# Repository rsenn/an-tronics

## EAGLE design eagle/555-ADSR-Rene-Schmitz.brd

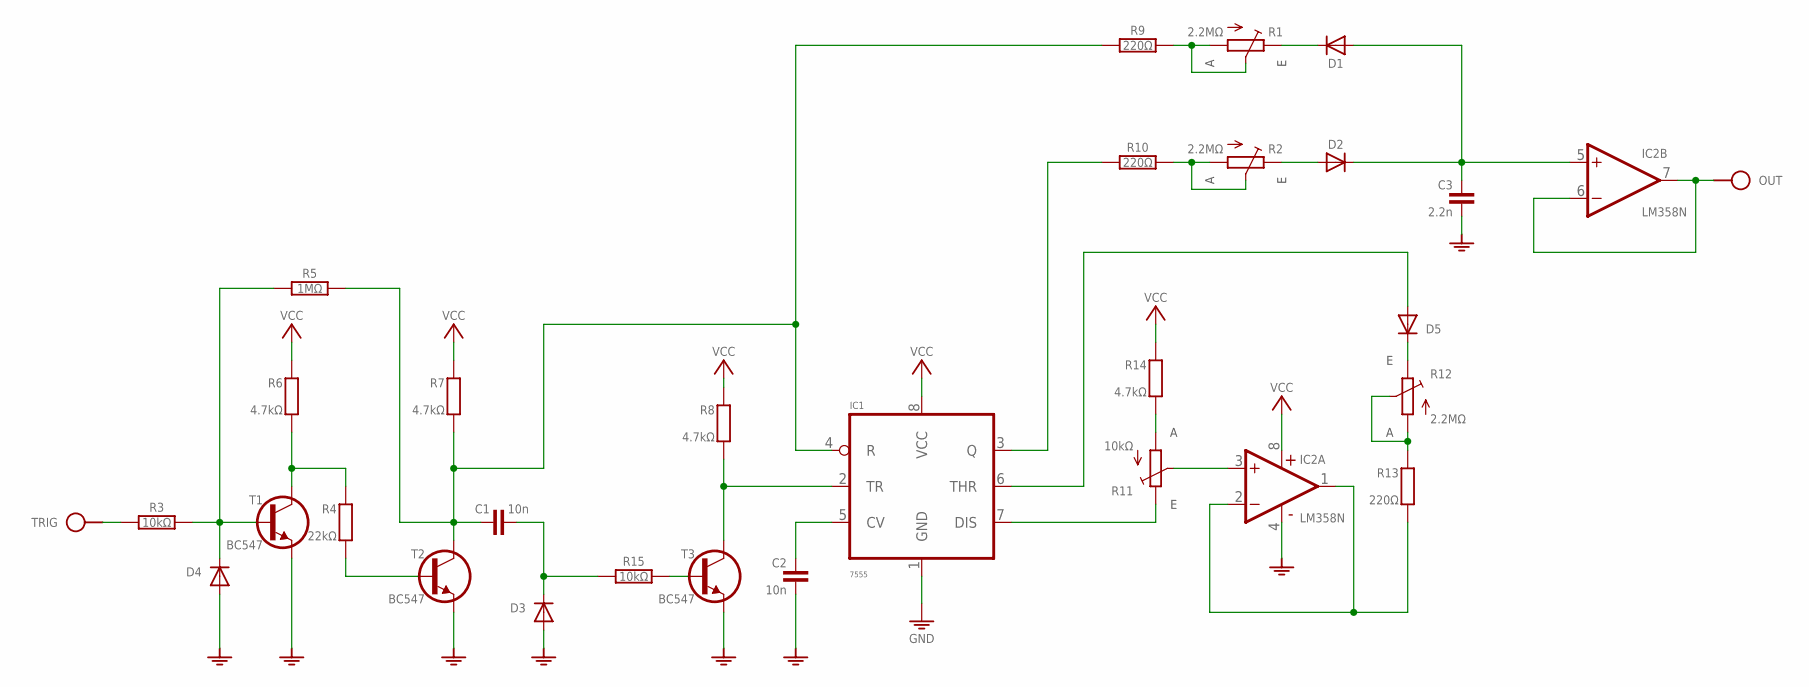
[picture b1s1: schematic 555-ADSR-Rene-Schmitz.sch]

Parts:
C1: 10n; C050-020X044
C2: 10n; C050-025X075/V
C3: 2.2n; C050-025X075/V
D1, D2: DIODE-HDO34-7; DO34-7
D3, D4, D5: DIODE34-7V; DO34-7V
IC1: 7555; DIL08
IC2: LM358N; DIL08
OUT: SPAD
R1, R2, R12: 2.2MΩ; R-TRIM
R3, R15: 10kΩ; 0204/10
R4: 22kΩ; 0204/10-V
R5: 1MΩ; 0204/10
R6, R7, R8, R14: 4.7kΩ; 0204/10
R9, R10: 220Ω; 0204/10
R11: 10kΩ; R-TRIM
R13: 220Ω; 0204/10-V
S2: VCC_GNDL; SPAD-+
T1, T2, T3: BC547; TO92-CBE
TRIG: SPAD

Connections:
GND: C2.2, C3.2, D3.A, D4.A, IC1.1 (GND), IC2.4 (V-), S2.1 (GND), T1.E, T2.E, T3.E
unnamed: R4.1, R6.2, T1.C
unnamed: R4.2, T2.B
unnamed: IC2.3 (+IN), R11.2 (S)
unnamed: D4.C, R3.2, R5.1, T1.B
unnamed: R15.2, T3.B
unnamed: R1.1 (A), R1.2 (S), R9.2
unnamed: R2.1 (A), R2.2 (S), R10.2
unnamed: R3.1, TRIG.1
unnamed: C1.1, IC1.4 (R), R5.2, R7.2, R9.1, T2.C
unnamed: IC1.2 (TR), R8.2, T3.C
unnamed: IC2.6 (-IN), IC2.7 (OUT), OUT.1
unnamed: C2.1, IC1.5 (CV)
unnamed: R12.1 (A), R12.2 (S), R13.1
unnamed: R11.1 (A), R14.2
unnamed: IC1.7 (DIS), R11.3 (E)
unnamed: D5.A, IC1.6 (THR)
unnamed: D5.C, R12.3 (E)
unnamed: C1.2, D3.C, R15.1
unnamed: IC1.3 (Q), R10.1
unnamed: D2.A, R2.3 (E)
unnamed: D1.C, R1.3 (E)
unnamed: IC2.1 (OUT), IC2.2 (-IN), R13.2
unnamed: C3.1, D1.A, D2.C, IC2.5 (+IN)
VCC: IC1.8 (VCC), IC2.8 (V+), R6.1, R7.1, R8.1, R14.1, S2.2 (VCC)

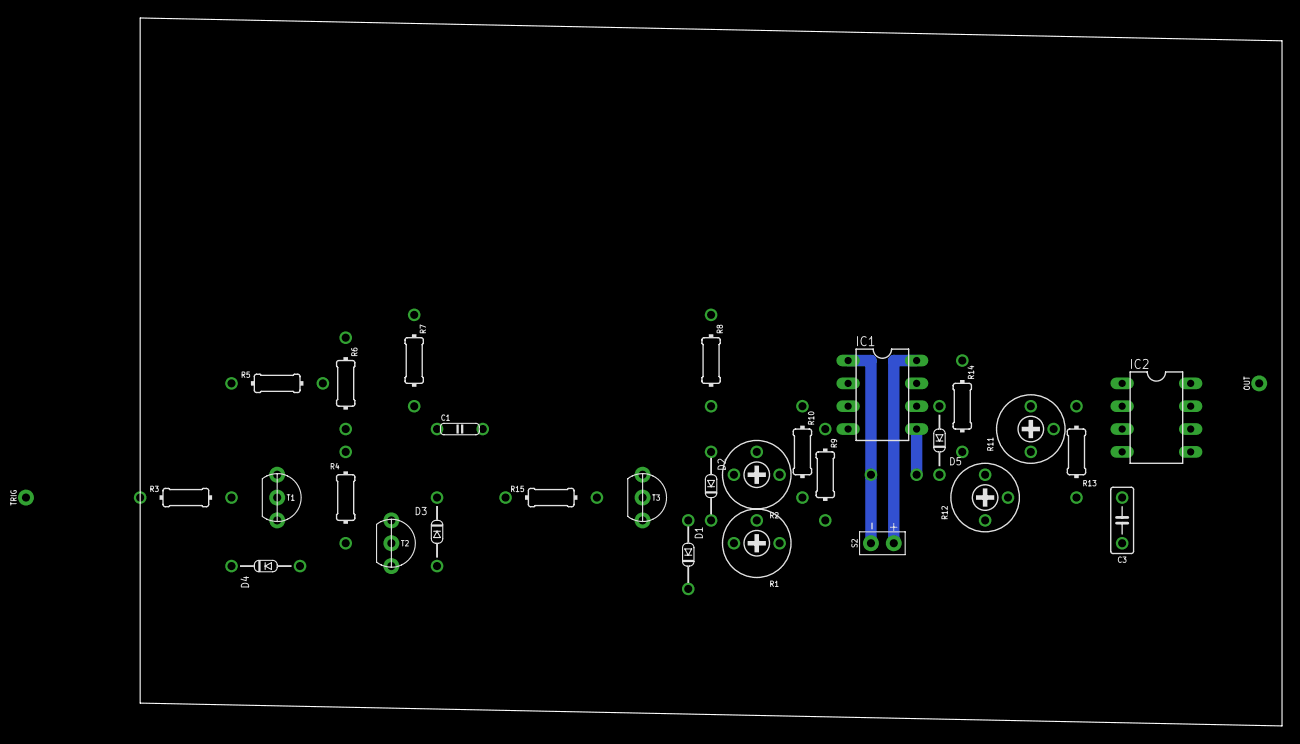
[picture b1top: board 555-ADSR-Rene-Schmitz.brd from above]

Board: 2 copper layers, 127.0 x 78.7 mm, 31 parts (1 on the bottom side), 25 nets.

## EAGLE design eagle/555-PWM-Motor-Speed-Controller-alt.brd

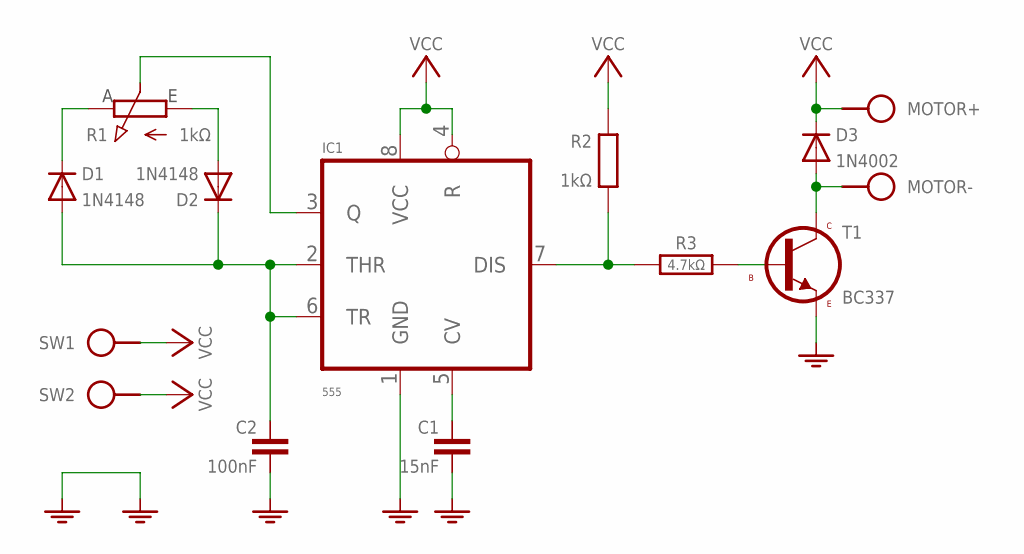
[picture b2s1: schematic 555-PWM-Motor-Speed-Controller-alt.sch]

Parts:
C1: 15nF; C050-020X036/V
C2: 100nF; C025-015X024/V
D1: 1N4148; DO34-5V
D2: 1N4148; DO34-5-V
D3: 1N4002; DO34-5V
IC1: 555; DIL08
MOTOR: SPAD+-+-; SPAD+-
PWR: VCC_GNDR; SPAD+-
R1: 1kΩ; CONN-3P/H
R2: 1kΩ; 0204/10-V
R3: 4.7kΩ; 0204/10-V
SW1, SW2: SPAD-1; SPAD
T1: BC337; TO92-CBE

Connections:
GND: C1.2, C2.2, IC1.1 (GND), PWR.1 (GND), T1.3 (E)
unnamed: C1.1, IC1.5 (CV)
unnamed: IC1.7 (DIS), R2.2 (1), R3.1
unnamed: IC1.3 (Q), R1.2 (S)
unnamed: D1.C, R1.3 (E)
unnamed: D2.A, R1.1 (A)
unnamed: C2.1, D1.A, D2.C, IC1.2 (THR), IC1.6 (TR)
unnamed: R3.2, T1.2 (B)
unnamed: D3.A, MOTOR.1, T1.1 (C)
PWR+: PWR.2 (VCC), SW1.1
VCC: D3.C, IC1.4 (R), IC1.8 (VCC), MOTOR.2, R2.1 (2), SW2.1

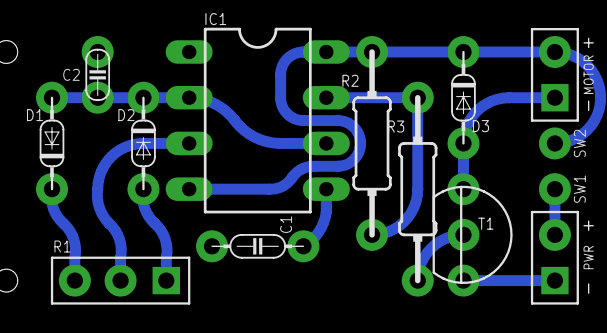
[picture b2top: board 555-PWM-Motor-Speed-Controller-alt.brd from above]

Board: 2 copper layers, 14 parts (0 on the bottom side), 11 nets.

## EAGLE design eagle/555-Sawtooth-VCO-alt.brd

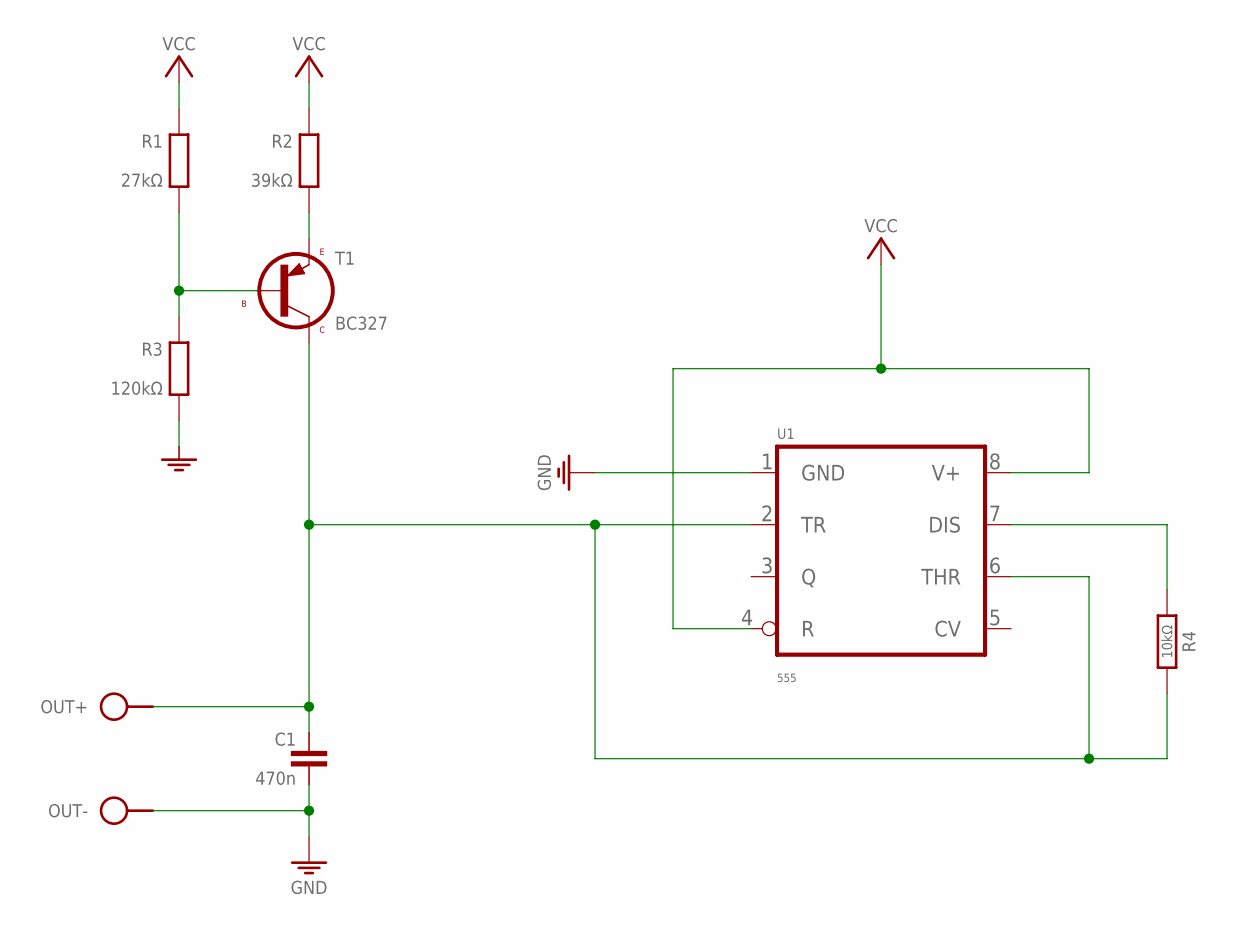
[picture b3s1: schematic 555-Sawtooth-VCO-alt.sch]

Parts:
C1: 470n; C075-020X044/V
OUT: SPAD+--+; SPAD-+
R1: 27kΩ; 0207/10
R2: 39kΩ; 0207/10
R3: 120kΩ; 0207/10
R4: 10kΩ; 0204/10
S3, S4, S5: VCC_GNDPWR-R; PWR-R
T1: BC327; TO92
U1: 555; DIL08

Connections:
DIS: C1.1, OUT.2, R4.2, T1.1 (C), U1.2 (TR), U1.6 (THR)
GND: C1.2, OUT.1, R3.2 (1), S4.1 (GND), S5.1 (GND), U1.1 (GND)
unnamed: R4.1, U1.7 (DIS)
unnamed: R2.2 (1), T1.3 (E)
unnamed: R1.2 (1), R3.1 (2), T1.2 (B)
VCC: R1.1 (2), R2.1 (2), S3.2 (VCC), U1.4 (R), U1.8 (V+)

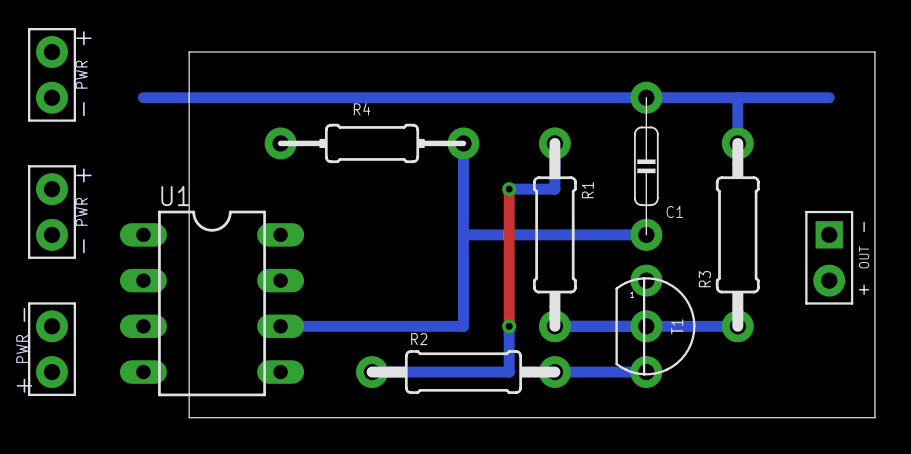
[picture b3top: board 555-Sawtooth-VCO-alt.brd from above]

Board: 2 copper layers, 38.1 x 20.3 mm, 11 parts (0 on the bottom side), 6 nets.

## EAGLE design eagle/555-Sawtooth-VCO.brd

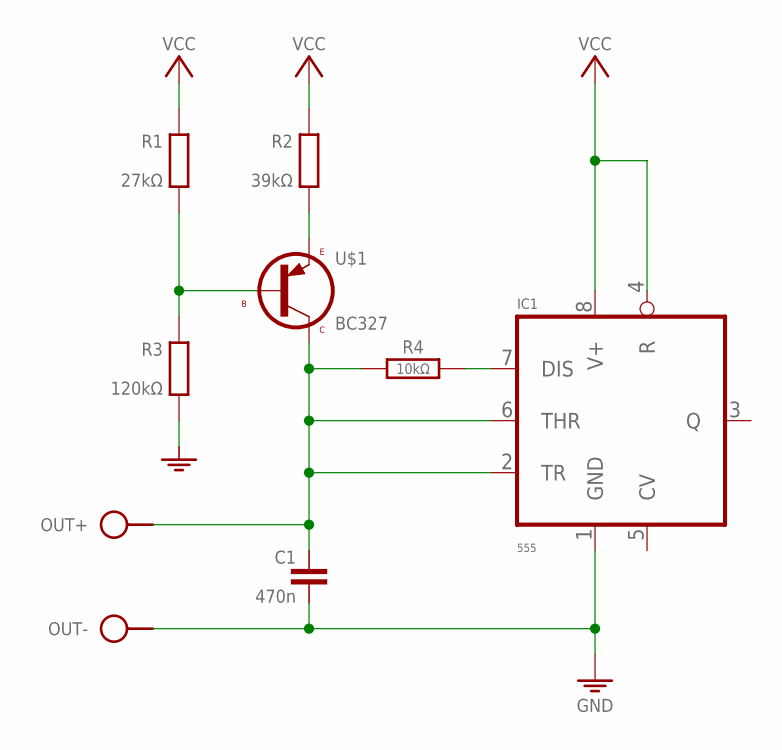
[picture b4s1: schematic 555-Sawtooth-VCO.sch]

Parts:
C1: 470n; C075-020X044/V
IC1: 555; DIL08
OUT: SPAD+--+; SPAD-+
R1: 27kΩ; 0207/10
R2: 39kΩ; 0207/10
R3: 120kΩ; 0207/10
R4: 10kΩ; 0204/10
S1: VCC_GNDPWR-R; PWR-R
U$1: BC327; TO92

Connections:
GND: C1.2, IC1.1 (GND), OUT.1, R3.2 (1), S1.1 (GND)
unnamed: IC1.7 (DIS), R4.2
unnamed: R2.2 (1), U$1.3 (E)
unnamed: R1.2 (1), R3.1 (2), U$1.2 (B)
TR: C1.1, IC1.2 (TR), IC1.6 (THR), OUT.2, R4.1, U$1.1 (C)
VCC: IC1.4 (R), IC1.8 (V+), R1.1 (2), R2.1 (2), S1.2 (VCC)

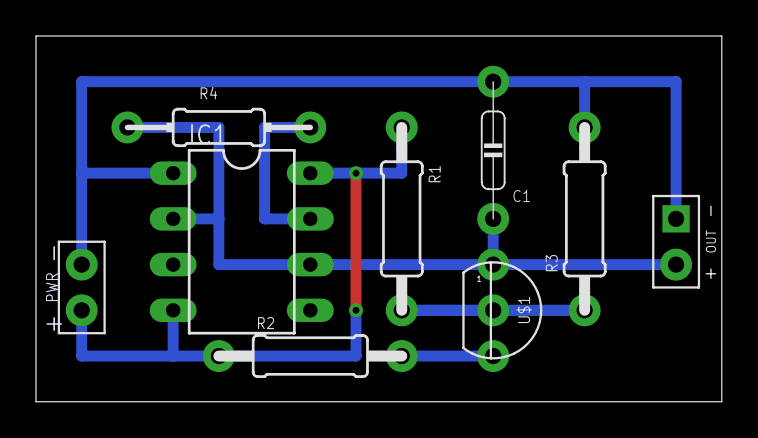
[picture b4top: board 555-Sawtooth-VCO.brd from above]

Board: 2 copper layers, 38.1 x 20.3 mm, 9 parts (0 on the bottom side), 6 nets.

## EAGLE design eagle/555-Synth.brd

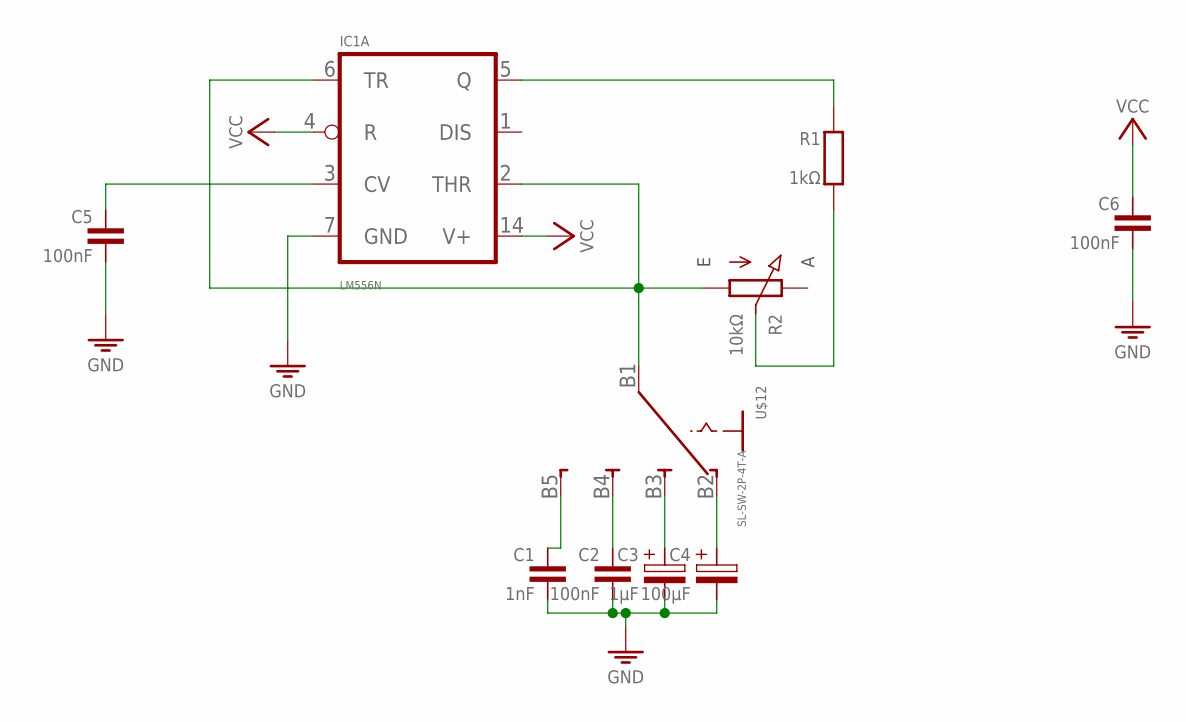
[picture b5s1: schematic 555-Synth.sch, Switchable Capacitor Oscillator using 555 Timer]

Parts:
C1: 1nF; C050-020X044/V
C2, C5, C6: 100nF; C050-020X044/V
C3: 1μF; E2,5-5/V
C4: 100μF; E2,5-5/V
IC1: LM556N; DIL14
J1: VCC_GNDL; SPAD-+
R1: 1kΩ; 0204/10-V
R2: 10kΩ; CONN-3P
U$1: SL-SW-2P-4T-A; SLSW-2P4T-2-H

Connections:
GND: C1.2, C2.2, C3.-, C4.-, C5.2, C6.2, IC1.7 (GND), J1.1 (GND)
unnamed: IC1.2 (THR), IC1.6 (TR), R2.1 (A), U$1.B1
unnamed: R1.2, R2.2 (S)
unnamed: IC1.5 (Q), R1.1
unnamed: C1.1, U$1.B5 (D)
unnamed: C2.1, U$1.B4 (C)
unnamed: C3.+, U$1.B3 (B)
unnamed: C4.+, U$1.B2 (A)
unnamed: C5.1, IC1.3 (CV)
VCC: C6.1, IC1.4 (R), IC1.14 (V+), J1.2 (VCC)

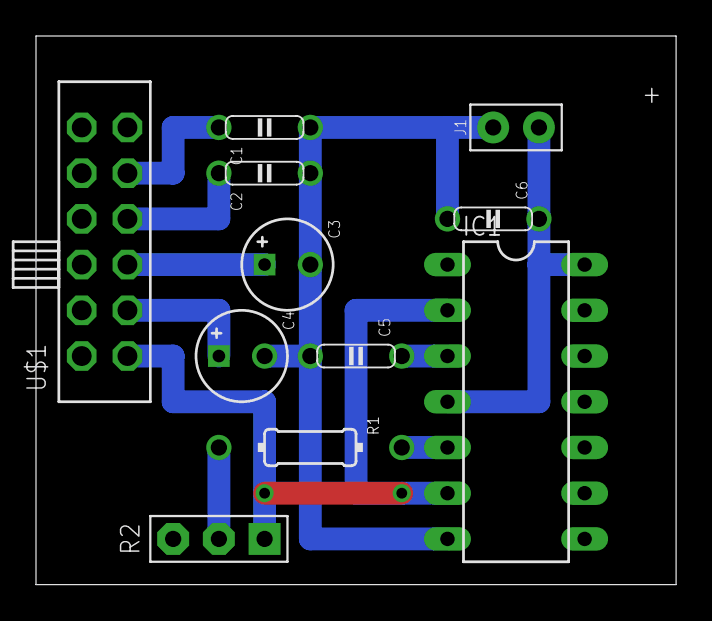
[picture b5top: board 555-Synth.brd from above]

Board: 2 copper layers, 35.6 x 30.5 mm, 11 parts (0 on the bottom side), 10 nets.

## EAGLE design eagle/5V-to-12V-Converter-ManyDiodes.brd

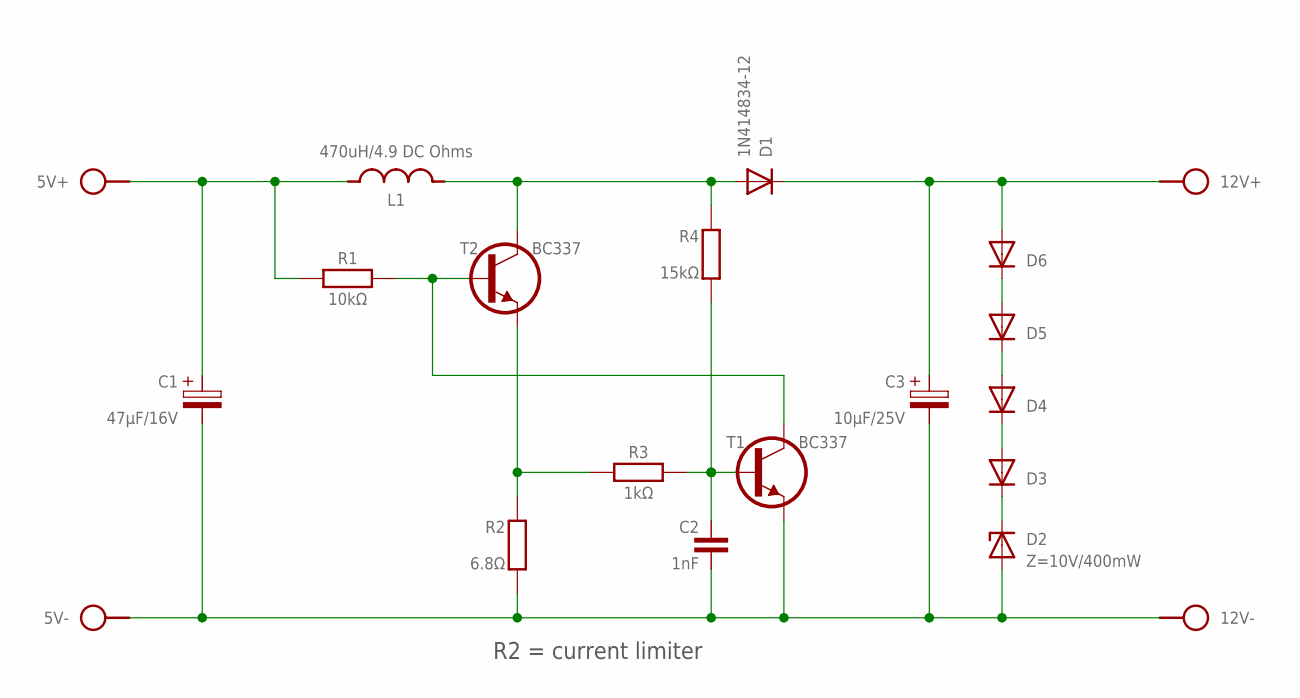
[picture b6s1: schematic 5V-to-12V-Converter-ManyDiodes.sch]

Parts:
5V: SPAD+--+; SPAD-+
12V: SPAD+-+-; SPAD+-
C1: 47μF/16V; E2.5-4/V
C2: 1nF; C050-020X036
C3: 10μF/25V; E2.5-4/V
D1: 1N414834-12; DO34-12
D2: Z=10V/400mW; DO35Z10/V
D3, D5: 1N4002-2.54A; DO35-2_54A
D4, D6: 1N4002-2.54; DO35-2_54
L1: 470uH/4.9 DC Ohms; ED16-X
R1: 10kΩ; 0204/7-V
R2: 6.8Ω; 0204/10
R3: 1kΩ; 0204/10
R4: 15kΩ; 0204/7-V
T1, T2: BC337; TO92-CBE

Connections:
GND: 5V.1, 12V.1, C1.-, C2.2, C3.-, D2.A, R2.1 (2), T1.E
unnamed: D2.C, D3.C
unnamed: 5V.2, C1.+, L1.1, R1.1
unnamed: 12V.2, C3.+, D1.C, D6.A
unnamed: R2.2 (1), R3.1, T2.E
unnamed: C2.1, R3.2, R4.1 (2), T1.B
unnamed: R1.2, T1.C, T2.B
unnamed: D1.A, L1.2, R4.2 (1), T2.C
unnamed: D3.A, D4.C
unnamed: D4.A, D5.C
unnamed: D5.A, D6.C

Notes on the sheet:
R2 = current limiter

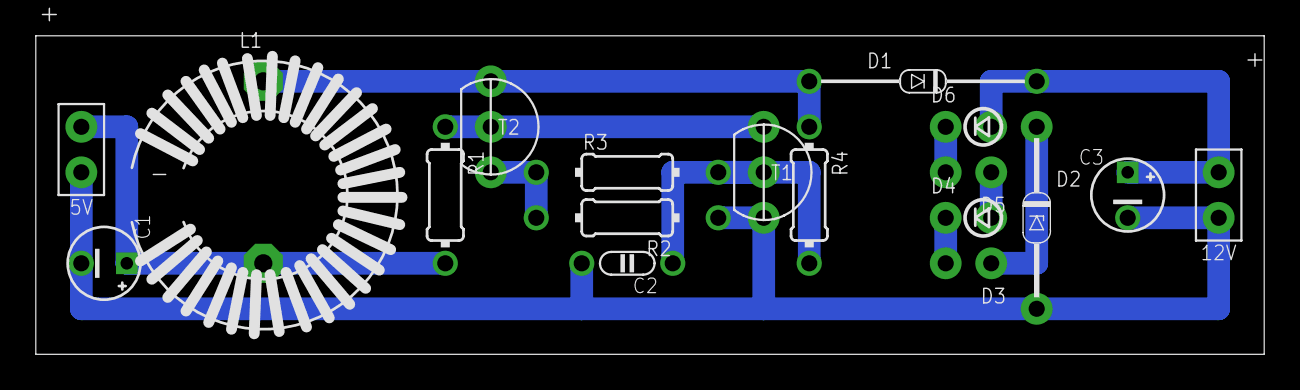
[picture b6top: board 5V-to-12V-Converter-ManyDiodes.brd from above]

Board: 2 copper layers, 68.6 x 17.8 mm, 18 parts (0 on the bottom side), 11 nets.
